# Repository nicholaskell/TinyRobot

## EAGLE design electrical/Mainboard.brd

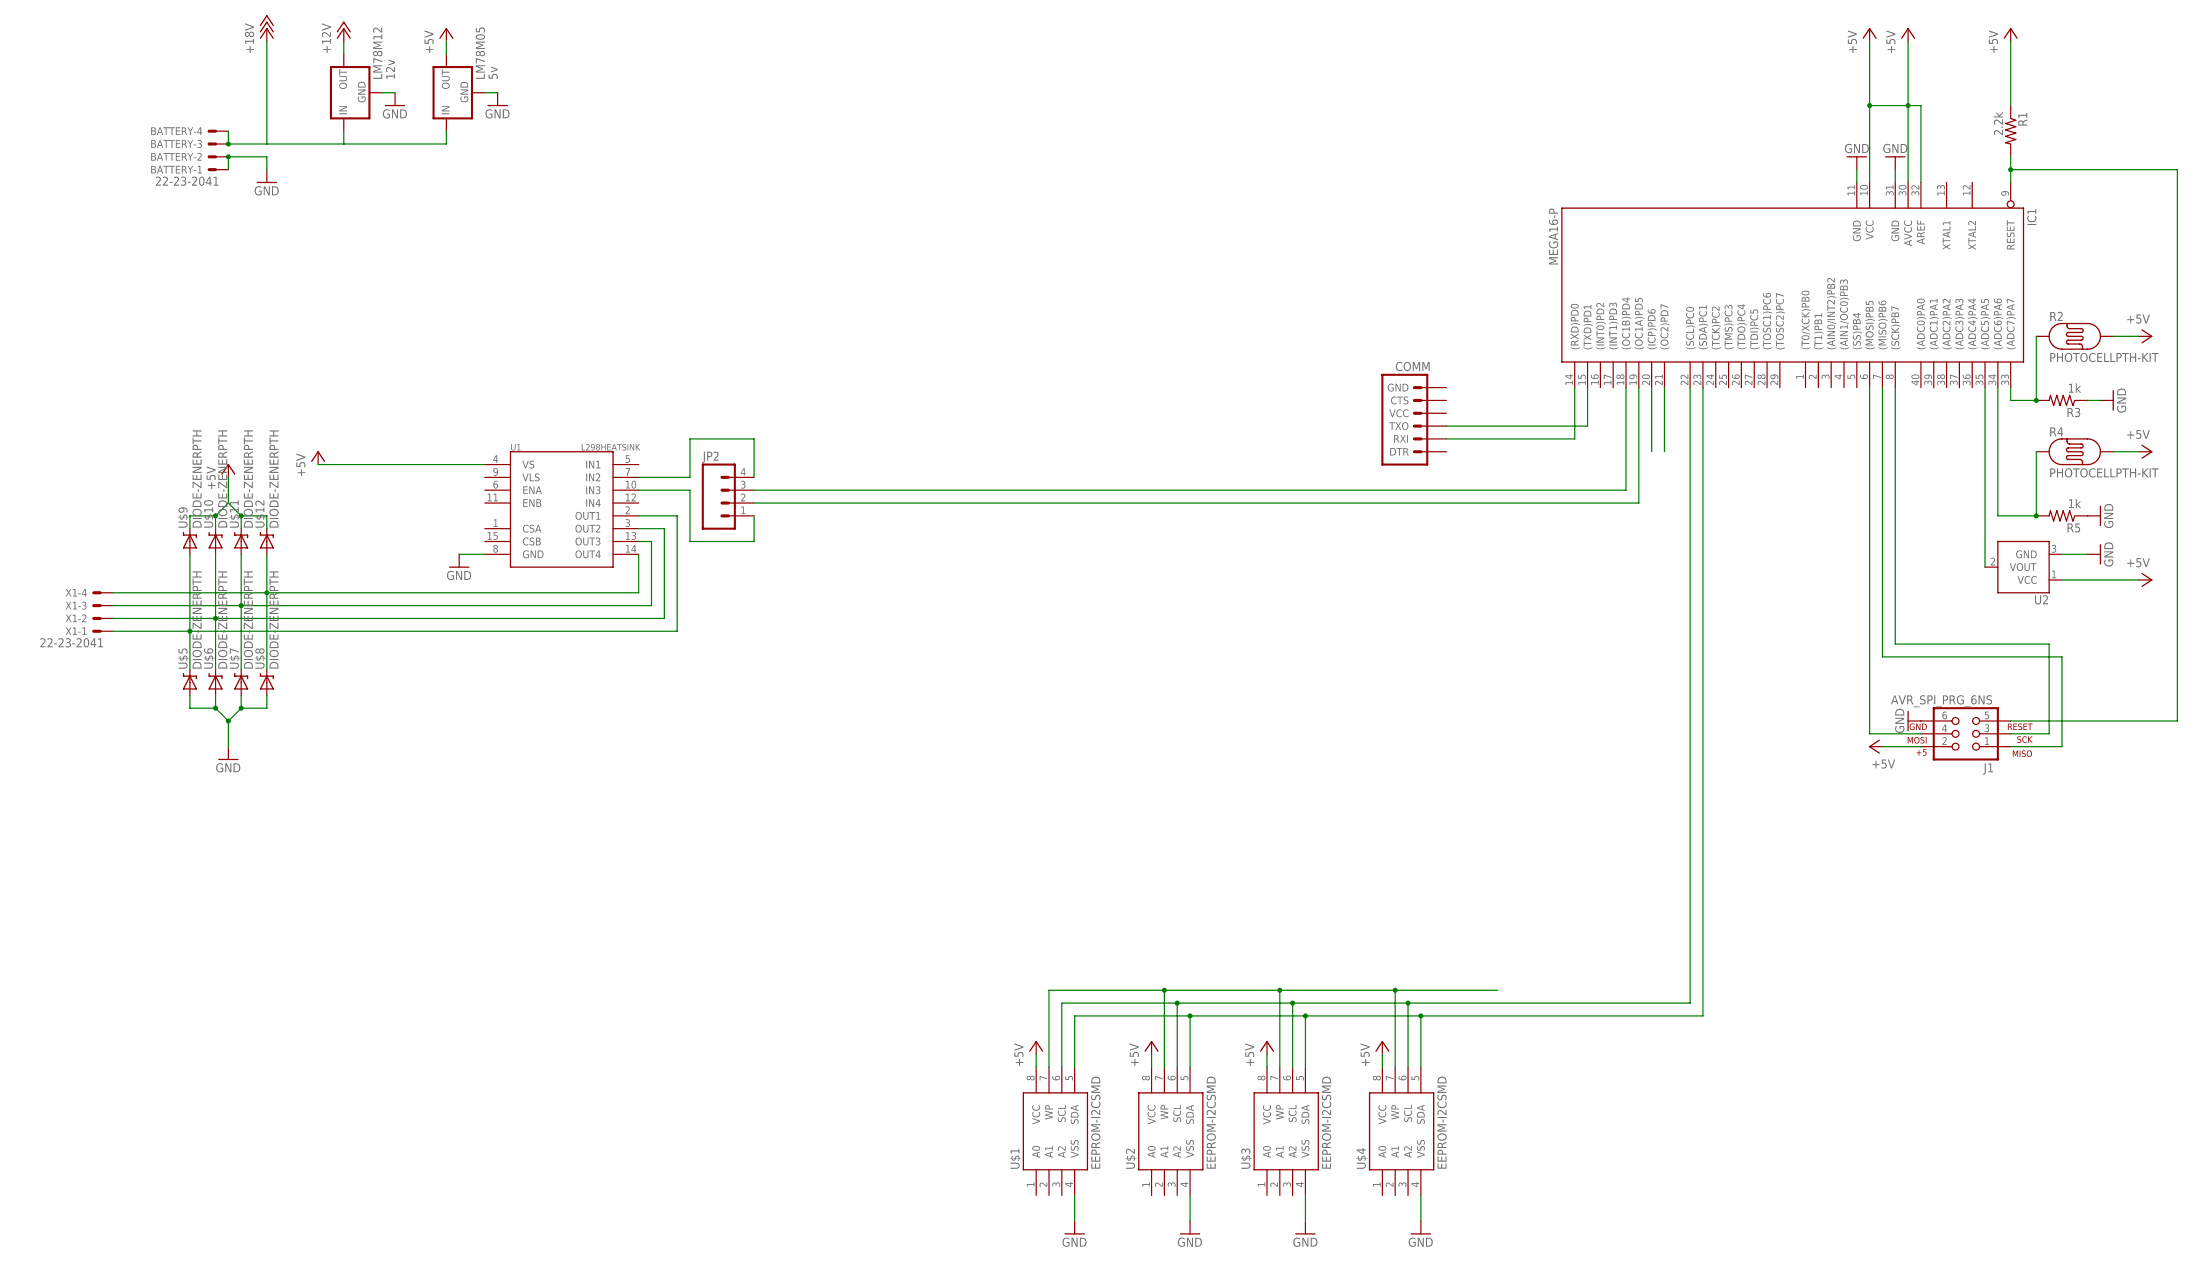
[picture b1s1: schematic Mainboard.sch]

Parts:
BATTERY: 22-23-2041
COMM: ARDUINO_SERIAL_PROGRAMPTH; 1X06
IC1: MEGA16-P; DIL40
J1: AVR_SPI_PRG_6NS; 2X3-NS
JP2: M04PTH; 1X04
LM78M05: 5v; 78MXXL
LM78M12: 12v; 78MXXL
R1: 2.2k; AXIAL-0.3
R2, R4: PHOTOCELLPTH-KIT; PHOTOCELL-KIT
R3, R5: 1k; AXIAL-0.3-KIT
U1: L298HEATSINK; MULTIWATT15_6400BGHEATSINK
U2: TMP36TO-92-KIT; TO-92-KIT
U$1, U$2, U$3, U$4: EEPROM-I2CSMD; SO08
U$5, U$6, U$7, U$8, U$9, U$10, U$11, U$12: DIODE-ZENERPTH; DIODE-ZENER
X1: 22-23-2041

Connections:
+5V: IC1.10 (VCC), IC1.30 (AVCC), IC1.32 (AREF), J1.2, LM78M05.OUT, R1.P$1 (1), R2.2, R4.2, U1.4 (VS), U2.1 (VCC), U$1.8 (VCC), U$2.8 (VCC), U$3.8 (VCC), U$4.8 (VCC), U$9.P$1 (C), U$10.P$1 (C), U$11.P$1 (C), U$12.P$1 (C)
+12V: LM78M12.OUT
+18V: BATTERY.3, BATTERY.4, LM78M05.IN, LM78M12.IN
GND: BATTERY.1, BATTERY.2, IC1.11 (GND), IC1.31 (GND), J1.6, LM78M05.GND, LM78M12.GND, R3.P$1 (1), R5.P$1 (1), U1.8 (GND), U2.3 (GND), U$1.4 (VSS), U$2.4 (VSS), U$3.4 (VSS), U$4.4 (VSS), U$5.P$2 (A), U$6.P$2 (A), U$7.P$2 (A), U$8.P$2 (A)
MOTOR_A: JP2.4, U1.7 (IN2)
unnamed: IC1.9 (RESET), J1.5, R1.P$2 (2)
unnamed: IC1.23 ((SDA)PC1), U$1.5 (SDA), U$2.5 (SDA), U$3.5 (SDA), U$4.5 (SDA)
unnamed: IC1.22 ((SCL)PC0), U$1.6 (SCL), U$2.6 (SCL), U$3.6 (SCL), U$4.6 (SCL)
unnamed: U$1.7 (WP), U$2.7 (WP), U$3.7 (WP), U$4.7 (WP)
unnamed: IC1.6 ((MOSI)PB5), J1.4
unnamed: IC1.34 ((ADC6)PA6), R4.1, R5.P$2 (2)
unnamed: IC1.7 ((MISO)PB6), J1.1
unnamed: IC1.33 ((ADC7)PA7), R2.1, R3.P$2 (2)
unnamed: IC1.8 ((SCK)PB7), J1.3
unnamed: IC1.35 ((ADC5)PA5), U2.2 (VOUT)
unnamed: IC1.19 ((OC1A)PD5), JP2.2
unnamed: IC1.18 ((OC1B)PD4), JP2.3
unnamed: COMM.2 (RXI), IC1.14 ((RXD)PD0)
unnamed: COMM.3 (TXO), IC1.15 ((TXD)PD1)
unnamed: JP2.1, U1.10 (IN3)
unnamed: U1.14 (OUT4), U$8.P$1 (C), U$12.P$2 (A), X1.4
unnamed: U1.3 (OUT2), U$6.P$1 (C), U$10.P$2 (A), X1.2
unnamed: U1.2 (OUT1), U$5.P$1 (C), U$9.P$2 (A), X1.1
unnamed: U1.13 (OUT3), U$7.P$1 (C), U$11.P$2 (A), X1.3

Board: 2 copper layers, 27 parts (0 on the bottom side), 23 nets, no tracks yet.

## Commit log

2012-06-07 Init TinyRobot
2012-06-07 Added Main Sproket drawing

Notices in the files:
parts and their libraries:
SparkFun-PowerIC: Licensing: CC v3.0 Share-Alike You are welcome to use this library for commercial purposes.
